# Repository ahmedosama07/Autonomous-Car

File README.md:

# Autonomous-Car
Autonomous car project for microprocessors course (EEC 243)
Line follower PID robot using ESP32 dev kit. The robot uses two DC motors with an [h-bridge](https://github.com/ahmedosama07/mDriverL298n/) and five IR TCRT5000 sensor modules.

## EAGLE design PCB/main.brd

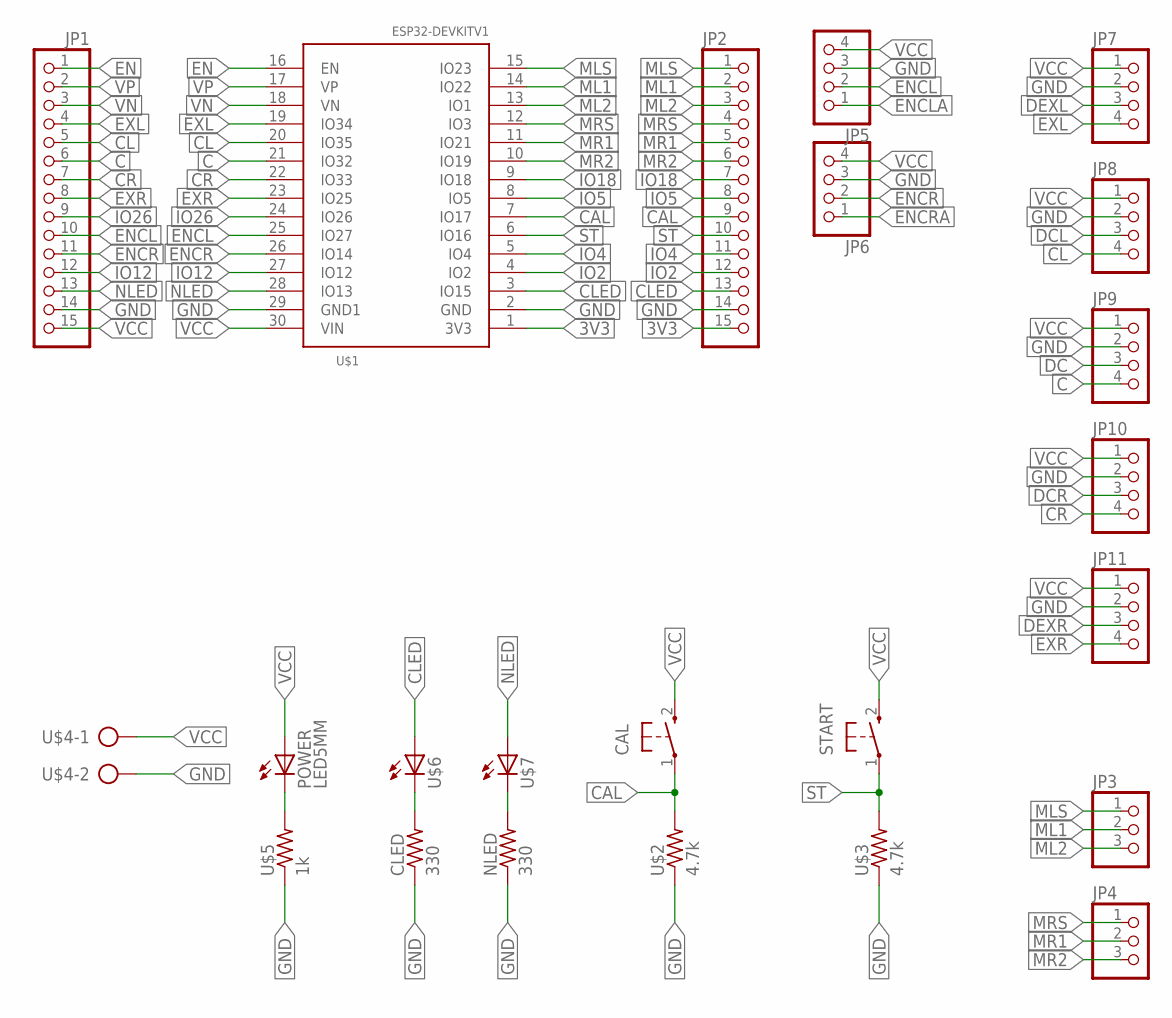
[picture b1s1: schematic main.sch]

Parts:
CAL: PUSH_BUTTON; B3F-10XX
CLED: 330; 0204/7
JP1, JP2: PINHD-1X15; 1X15
JP3, JP4: PINHD-1X3; 1X03
JP5, JP6, JP7, JP8, JP9, JP10, JP11: PINHD-1X4; 1X04
NLED: 330; 0204/7
POWER: LED5MM
START: PUSH_BUTTON; B3F-10XX
U$1: ESP32DEVKITV1; ESP32-DEVKITV1
U$2, U$3: 4.7k; 0204/7
U$4: CON_PTR_2(V_2); AK300/2
U$5: 1k; 0204/7
U$6, U$7: LED5MM

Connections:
3V3: JP2.15, U$1.1 (3V3)
C: JP1.6, JP9.4, U$1.21 (IO32)
CAL: CAL.1, JP2.9, U$1.7 (IO17), U$2.2
CL: JP1.5, JP8.4, U$1.20 (IO35)
CLED: JP2.13, U$1.3 (IO15), U$6.A
CR: JP1.7, JP10.4, U$1.22 (IO33)
DC: JP9.3
DCL: JP8.3
DCR: JP10.3
DEXL: JP7.3
DEXR: JP11.3
EN: JP1.1, U$1.16 (EN)
ENCL: JP1.10, JP5.2, U$1.25 (IO27)
ENCLA: JP5.1
ENCR: JP1.11, JP6.2, U$1.26 (IO14)
ENCRA: JP6.1
EXL: JP1.4, JP7.4, U$1.19 (IO34)
EXR: JP1.8, JP11.4, U$1.23 (IO25)
GND: CLED.1, JP1.14, JP2.14, JP5.3, JP6.3, JP7.2, JP8.2, JP9.2, JP10.2, JP11.2, NLED.1, U$1.2 (GND), U$1.29 (GND1), U$2.1, U$3.1, U$4.2, U$5.1
IO2: JP2.12, U$1.4 (IO2)
IO4: JP2.11, U$1.5 (IO4)
IO5: JP2.8, U$1.8 (IO5)
IO12: JP1.12, U$1.27 (IO12)
IO18: JP2.7, U$1.9 (IO18)
IO26: JP1.9, U$1.24 (IO26)
ML1: JP2.2, JP3.2, U$1.14 (IO22)
ML2: JP2.3, JP3.3, U$1.13 (IO1)
MLS: JP2.1, JP3.1, U$1.15 (IO23)
MR1: JP2.5, JP4.2, U$1.11 (IO21)
MR2: JP2.6, JP4.3, U$1.10 (IO19)
MRS: JP2.4, JP4.1, U$1.12 (IO3)
unnamed: POWER.K (C), U$5.2
unnamed: CLED.2, U$6.K (C)
unnamed: NLED.2, U$7.K (C)
NLED: JP1.13, U$1.28 (IO13), U$7.A
ST: JP2.10, START.1, U$1.6 (IO16), U$3.2
VCC: CAL.2 (S), JP1.15, JP5.4, JP6.4, JP7.1, JP8.1, JP9.1, JP10.1, JP11.1, POWER.A, START.2 (S), U$1.30 (VIN), U$4.1
VN: JP1.3, U$1.18 (VN)
VP: JP1.2, U$1.17 (VP)

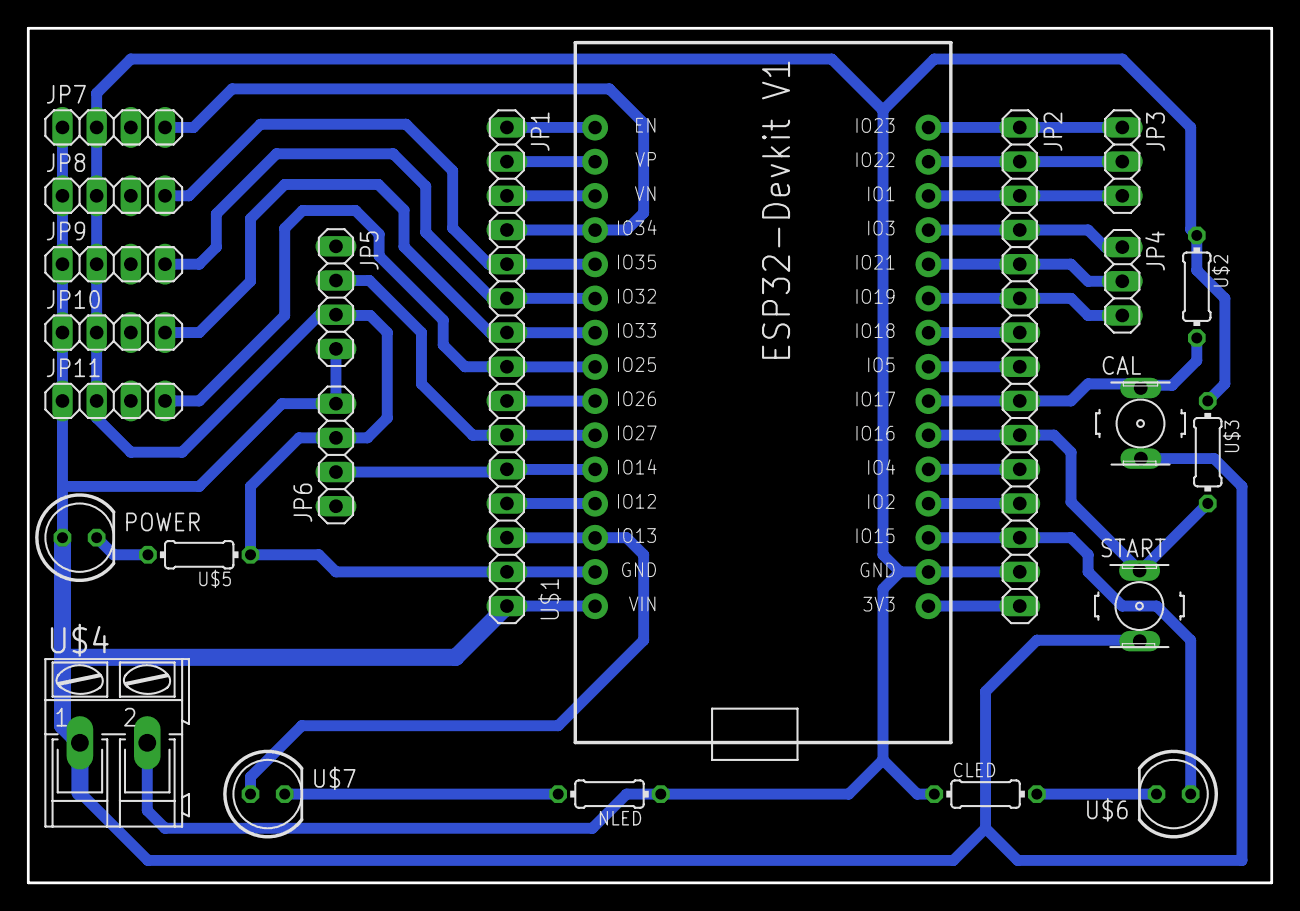
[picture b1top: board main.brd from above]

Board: 2 copper layers, 92.4 x 63.5 mm, 23 parts (0 on the bottom side), 32 nets.

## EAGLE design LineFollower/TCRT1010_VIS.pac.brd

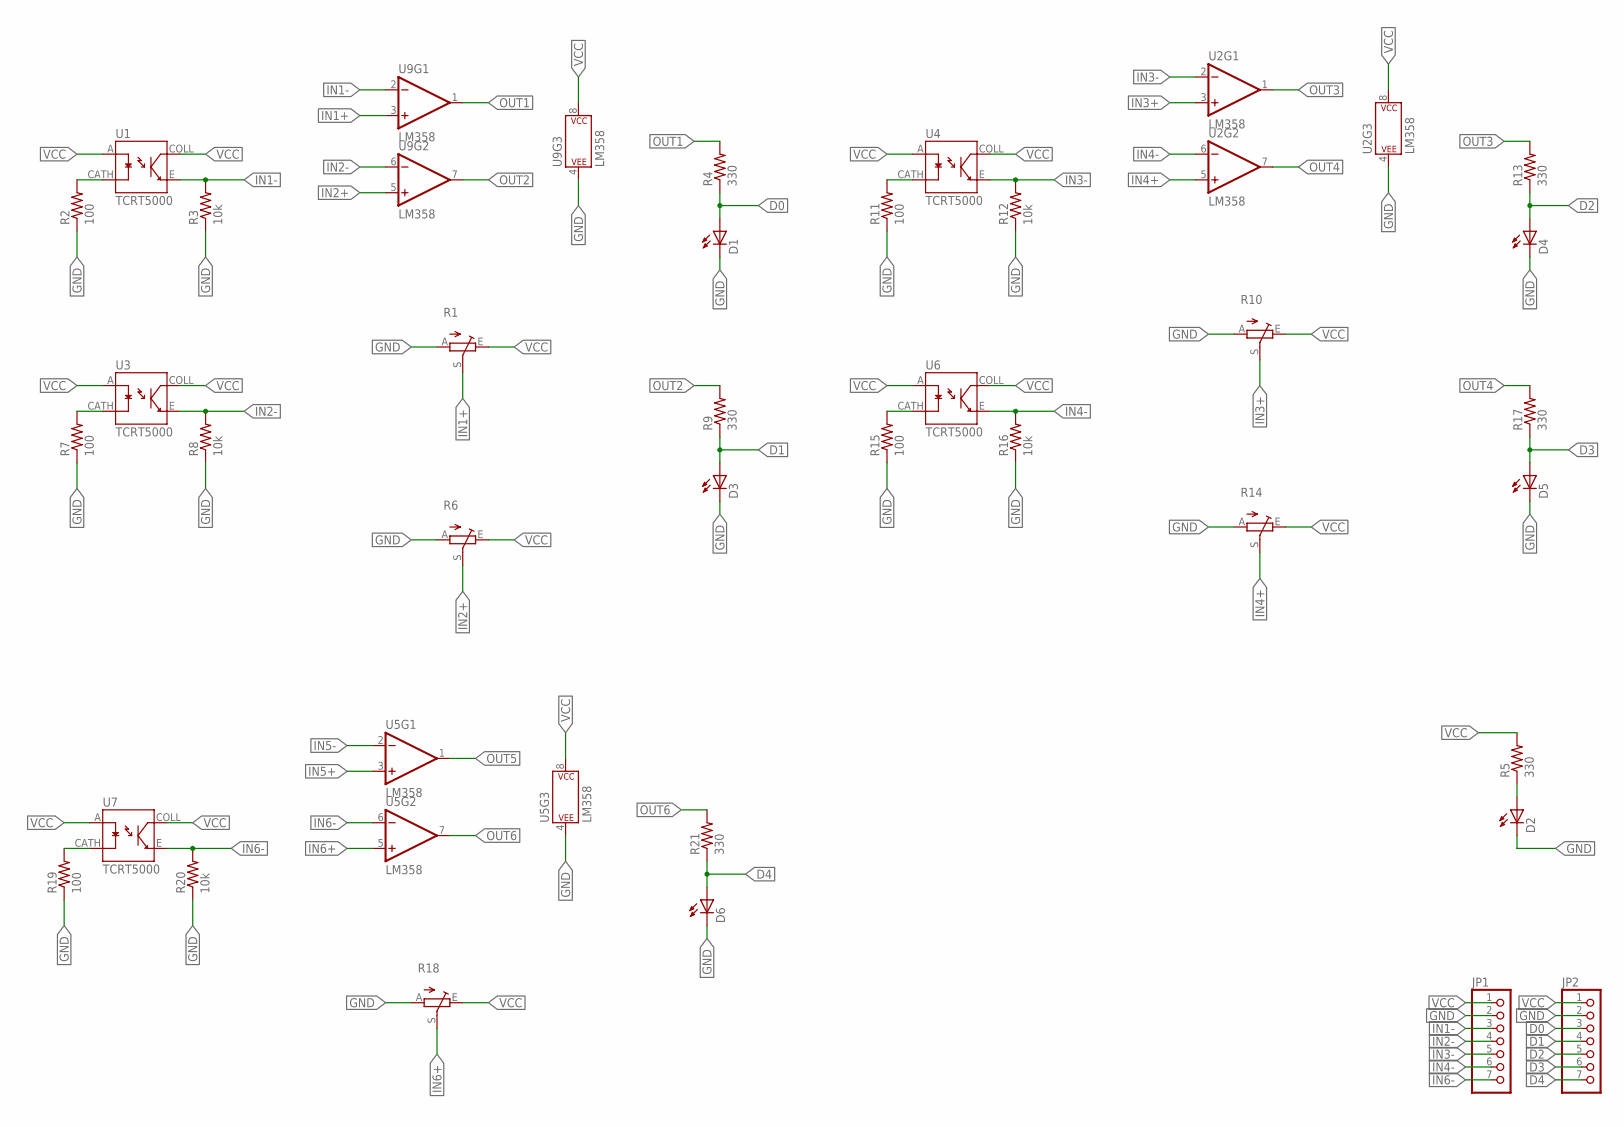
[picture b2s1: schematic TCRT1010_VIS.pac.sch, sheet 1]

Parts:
D1, D2, D3, D4, D5, D6: LED5MM
JP1, JP2: PINHD-1X7; 1X07
R1, R6, R10, R14, R18: TRIM_EU-CA6V; CA6V
R2, R7, R11, R15, R19: 100; 0204/7
R3, R8, R12, R16, R20: 10k; 0204/7
R4, R5, R9, R13, R17, R21: 330; 0204/7
U1, U3, U4, U6, U7: TCRT5000; OPTO_TCRT5000
U2, U5, U9: LM358; DIP08

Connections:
D0: D1.A, JP2.3, R4.1
D1: D3.A, JP2.4, R9.1
D2: D4.A, JP2.5, R13.1
D3: D5.A, JP2.6, R17.1
D4: D6.A, JP2.7, R21.1
GND: D1.K (C), D2.K (C), D3.K (C), D4.K (C), D5.K (C), D6.K (C), JP1.2, JP2.2, R1.A, R2.1, R3.1, R6.A, R7.1, R8.1, R10.A, R11.1, R12.1, R14.A, R15.1, R16.1, R18.A, R19.1, R20.1, U2.4 (P$V-), U5.4 (P$V-), U9.4 (P$V-)
IN1+: R1.S, U9.3 (+IN)
IN1-: JP1.3, R3.2, U1.E, U9.2 (-IN)
IN2+: R6.S, U9.5 (+IN)
IN2-: JP1.4, R8.2, U3.E, U9.6 (-IN)
IN3+: R10.S, U2.3 (+IN)
IN3-: JP1.5, R12.2, U2.2 (-IN), U4.E
IN4+: R14.S, U2.5 (+IN)
IN4-: JP1.6, R16.2, U2.6 (-IN), U6.E
IN5+: U5.3 (+IN)
IN5-: U5.2 (-IN)
IN6+: R18.S, U5.5 (+IN)
IN6-: JP1.7, R20.2, U5.6 (-IN), U7.E
unnamed: R2.2, U1.CATH
unnamed: D2.A, R5.1
unnamed: R7.2, U3.CATH
unnamed: R11.2, U4.CATH
unnamed: R15.2, U6.CATH
unnamed: R19.2, U7.CATH
OUT1: R4.2, U9.1 (OUT)
OUT2: R9.2, U9.7 (OUT)
OUT3: R13.2, U2.1 (OUT)
OUT4: R17.2, U2.7 (OUT)
OUT5: U5.1 (OUT)
OUT6: R21.2, U5.7 (OUT)
VCC: JP1.1, JP2.1, R1.E, R5.2, R6.E, R10.E, R14.E, R18.E, U1.A, U1.COLL, U2.8 (P$V+), U3.A, U3.COLL, U4.A, U4.COLL, U5.8 (P$V+), U6.A, U6.COLL, U7.A, U7.COLL, U9.8 (P$V+)

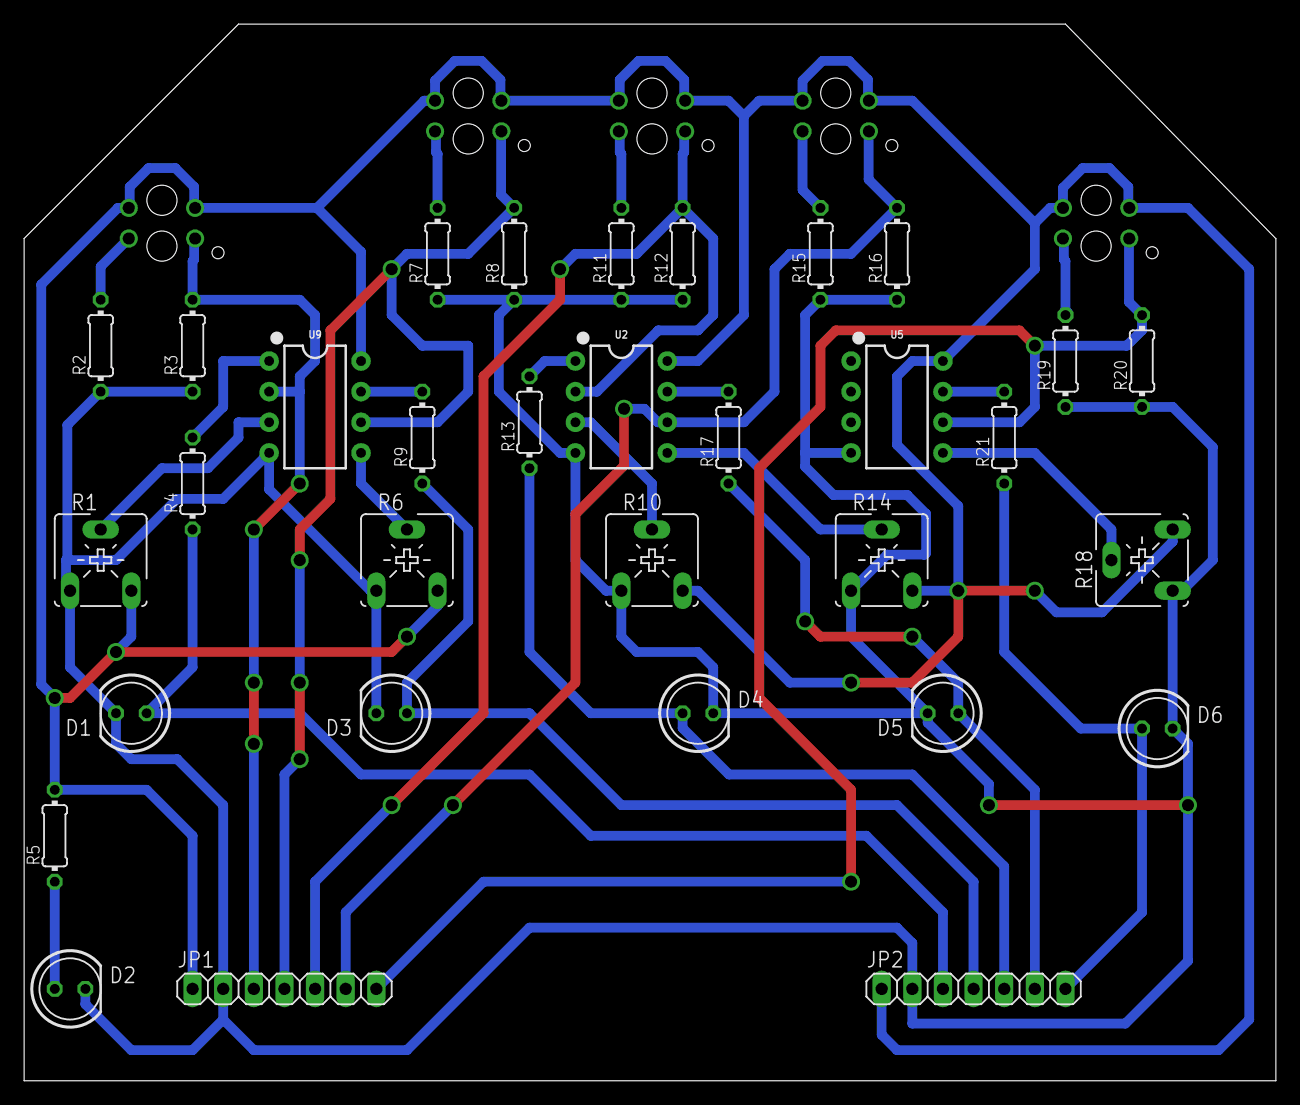
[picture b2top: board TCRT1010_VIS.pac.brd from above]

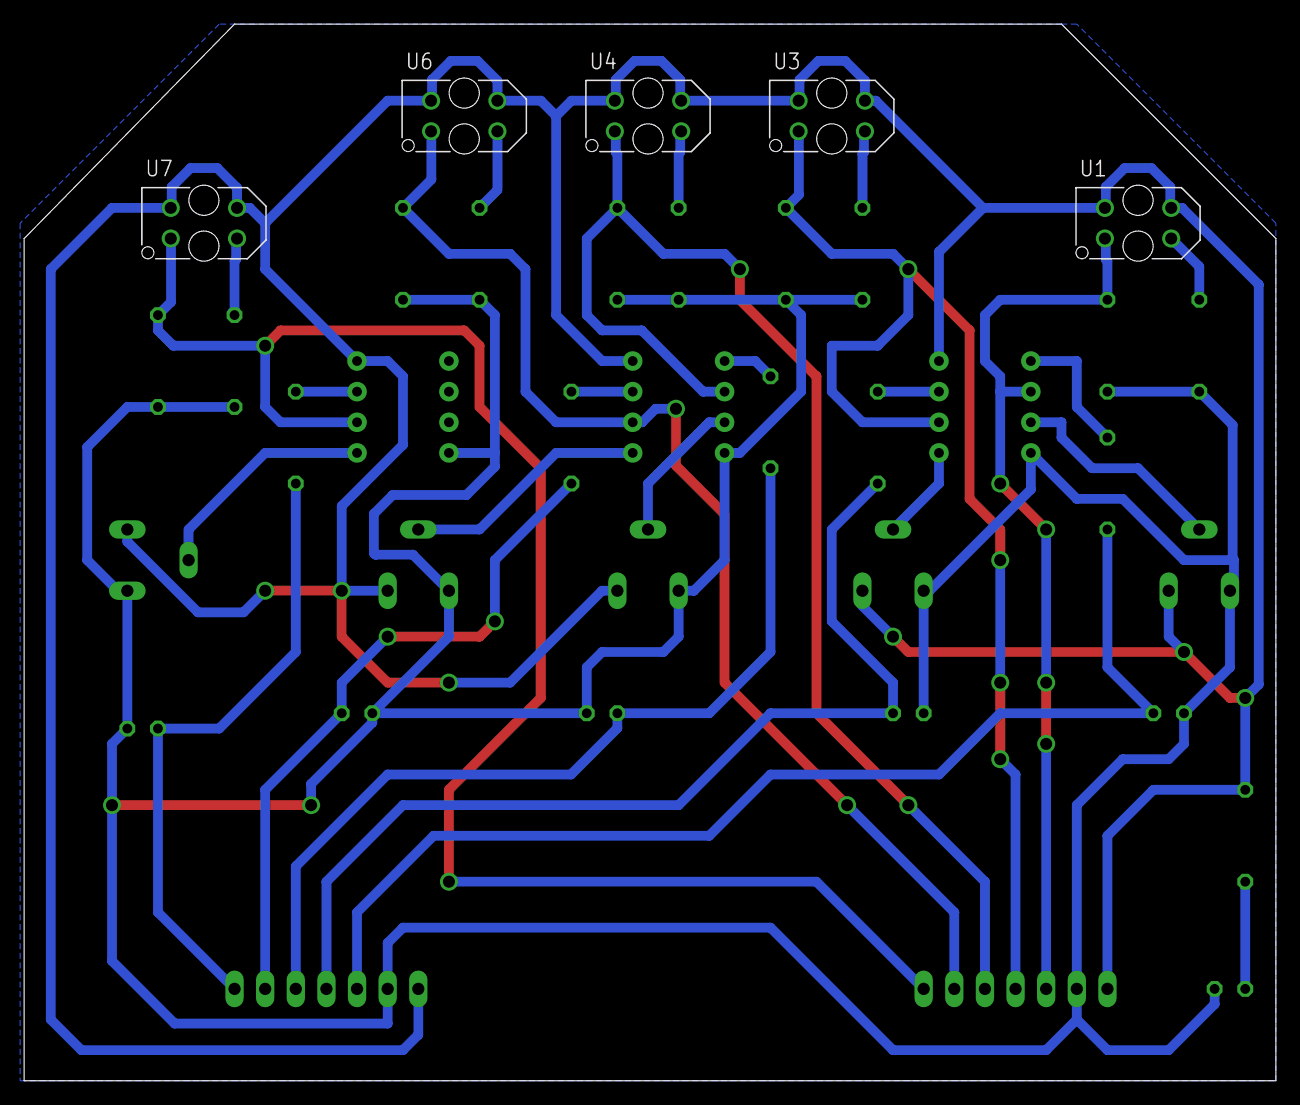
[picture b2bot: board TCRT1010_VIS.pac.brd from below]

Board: 2 copper layers, 103.8 x 87.6 mm, 37 parts (5 on the bottom side), 28 nets.

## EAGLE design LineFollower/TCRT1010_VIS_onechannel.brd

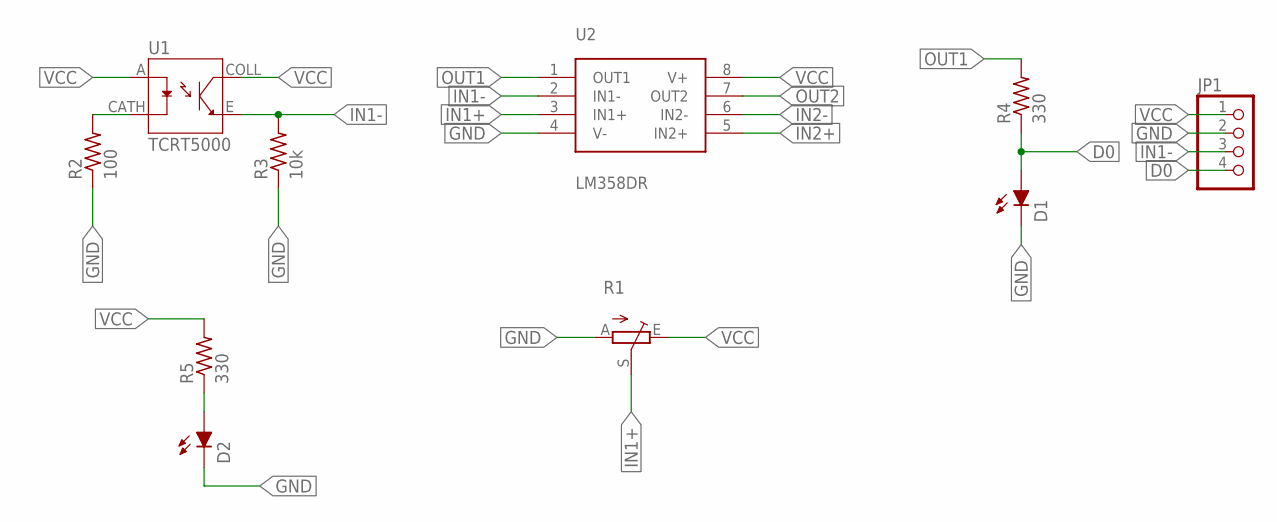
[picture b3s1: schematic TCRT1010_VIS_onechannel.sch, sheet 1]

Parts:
D1, D2: LED_LEDCHIP-LED0603MP; LED_CHIP-LED0603MP
JP1: PINHD-1X4; 1X04
R1: TRIM_EU-CA6V; CA6V
R2: 100; R0805
R3: 10k; R0603
R4, R5: 330; R0603
U1: TCRT5000; OPTO_TCRT5000
U2: LM358DR

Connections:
D0: D1.A, JP1.4, R4.1
GND: D1.C, D2.C, JP1.2, R1.A, R2.1, R3.1, U2.4 (V-)
IN1+: R1.S, U2.3 (IN1+)
IN1-: JP1.3, R3.2, U1.E, U2.2 (IN1-)
IN2+: U2.5 (IN2+)
IN2-: U2.6 (IN2-)
unnamed: R2.2, U1.CATH
unnamed: D2.A, R5.1
OUT1: R4.2, U2.1 (OUT1)
OUT2: U2.7 (OUT2)
VCC: JP1.1, R1.E, R5.2, U1.A, U1.COLL, U2.8 (V+)

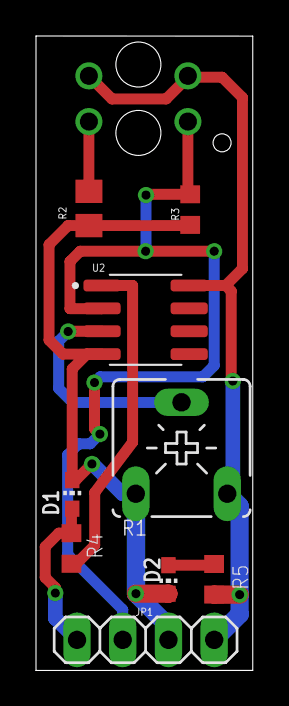
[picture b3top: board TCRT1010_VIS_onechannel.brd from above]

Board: 2 copper layers, 12.0 x 35.2 mm, 10 parts (1 on the bottom side), 8 nets.

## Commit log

2023-04-02 PID sample code
2023-04-24 Add files via upload
    first declerations withut functions
2023-04-24 experiment 1
2023-04-24 third
2023-04-24 last
2023-04-24 last2
2023-04-24 new pin names
2023-04-24 pin_names
2023-04-26 motor driver library and PID library
2023-04-26 added comments in code and removed unnecessary function
2023-04-26 Revert "Create README.md"
    This reverts commit 71a53a78075eb216c34a92f0033d326e7082d166.
2023-04-26 Revert "Revert "Create README.md""
    This reverts commit a09cfaec619d11aedcc8b14303b663fdedca9f33.
2023-04-26 Revert "added comments in code and removed unnecessary function"
    This reverts commit 791606d31dcf9939a1f476977160cbbe29ac3fbf.
2023-04-26 Code demo with PID
2023-04-30 Linefollower module single channel board
2023-04-30 update single channel
2023-04-30 5 channel module
2023-04-30 preview
2023-05-02 Fixed logical errors
2023-05-02 New PCB
2023-05-04 Working but needs tuning
2023-05-06 Better response
2023-05-06 decreased oscillations
2023-05-06 silly trial
2023-05-06 Stable
2023-05-06 Led switching
2023-05-07 Updated board and
2023-05-07 Updated directories
2023-05-07 First version of the report
2023-05-07 Adjusted speed
2023-05-07 Debugging via Bluetooth
2023-05-08 Working with Bluetooth
2023-05-08 simple mobile application
2023-05-08 Build
2023-05-08 Final release
2023-05-08 Using lower and upper
2023-05-08 Code refactor and meaningful messages
2023-05-08 Removing unused functions marked as comments.
2023-05-08 Final Code Screenshots and Adding References.
2023-05-08 Revert "Removing unused functions marked as comments."
    This reverts commit 6f1983459189a43fc3e1527c4519da61e39bfc3f.
2023-05-09 Rotation issues
2023-05-09 Cleaning
2023-05-10 Final report
